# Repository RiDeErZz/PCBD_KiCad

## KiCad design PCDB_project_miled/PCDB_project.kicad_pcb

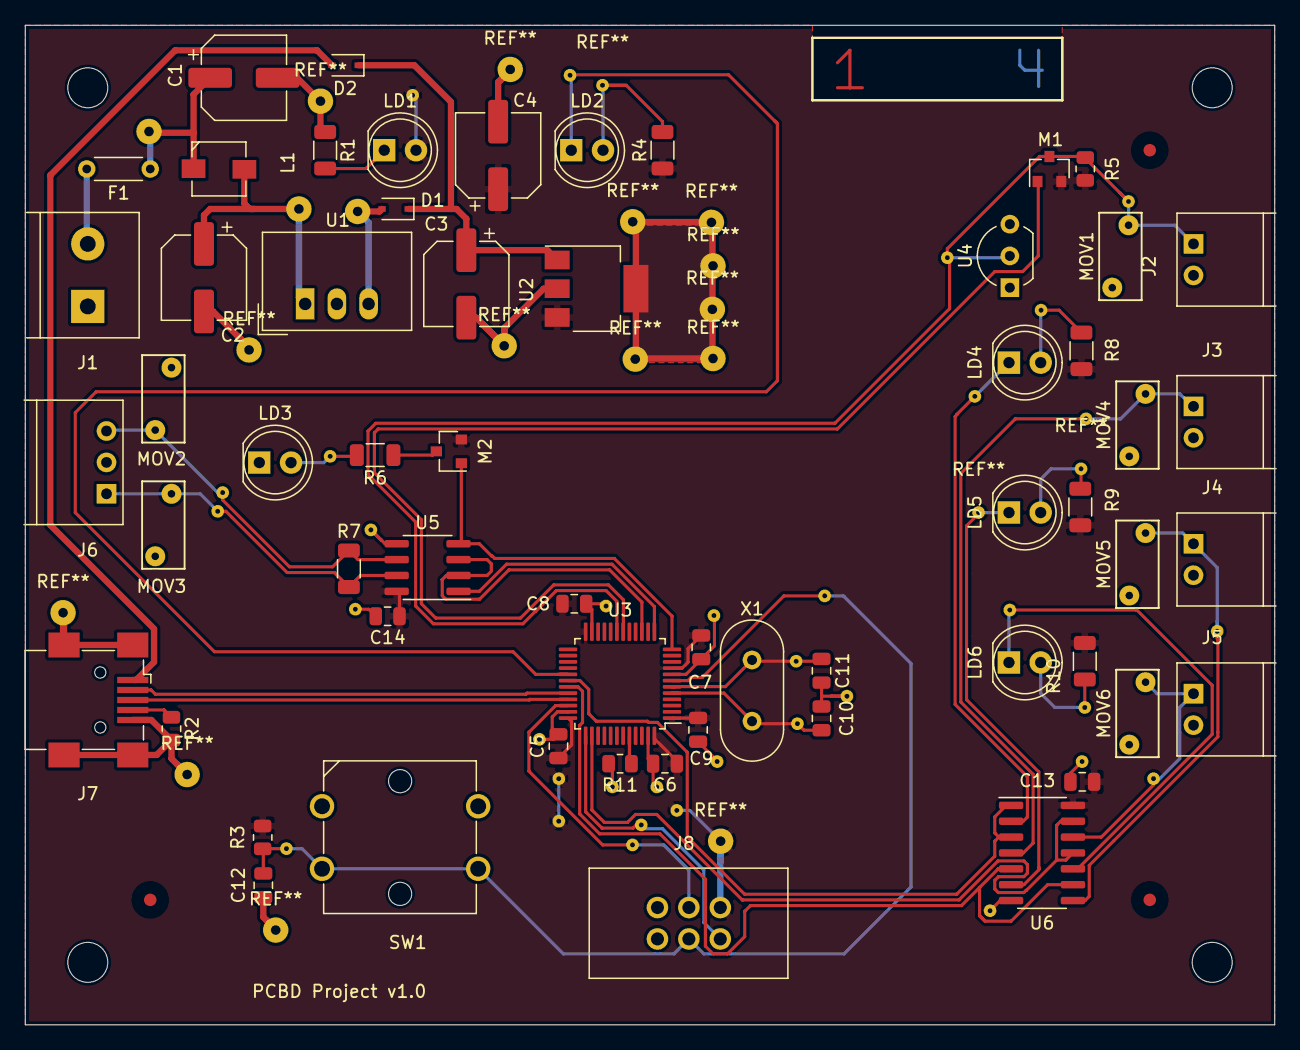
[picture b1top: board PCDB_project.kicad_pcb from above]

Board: 2 copper layers, 100.0 x 80.0 mm, 66 parts (0 on the bottom side), 41 nets.

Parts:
C1, C2, C3, C4: 10uF; CP_Elec_6.3x5.8
C5, C6, C7, C8, C9, C12, C13, C14: 100nF; C_0805_2012Metric
C10, C11: 20pF; C_0805_2012Metric
D1, D2: BAT60J; D_SOD-323
F1: 250mA; R_Axial_DIN0204_L3.6mm_D1.6mm_P5.08mm_Horizontal
FD1, FD2, FD3: Fiducial_1mm_Mask3mm
H1, H2, H3, H4: MountingHole_3.2mm_M3
J1: Power
J2, J3, J4, J5: 22-05-7025; IO2
J6: Comm; IO3
J7: USB_B_Mini; USB_Mini-B_Wuerth_65100516121_Horizontal
J8: Debug
L1: 5.6uH; tck141
LD1, LD6: Red; LED_D5.0mm
LD2: YELLOW; LED_D5.0mm
LD3: Green; LED_D5.0mm
LD4, LD5: Yellow; LED_D5.0mm
M1, M2: BSS84; SOT-23
MOV1, MOV2, MOV3, MOV4, MOV5, MOV6: MCFT000215; RV_Disc_D7mm_W3.4mm_P5mm
R1, R4, R6, R8, R9, R10: 330R; R_1206_3216Metric
R2, R11: 100k; R_0805_2012Metric
R3, R5: 4k7; R_0805_2012Metric
R7: 120R; R_1206_3216Metric
SW1: Reset; B3F-4000
U1: TSR_1-2450; Converter_DCDC_TRACO_TSR-1_THT
U2: UA78M33; SOT-223-3_TabPin2
U3: STM32F103CBT6; LQFP-48_7x7mm_P0.5mm
U4: DS1822-PAR; TO-92_Inline_Wide
U5: MAX3486; SOIC-8_3.9x4.9mm_P1.27mm
U6: MC74LCX07; SOIC-14_3.9x8.7mm_P1.27mm
X1: 8MHz; Crystal_HC18-U_Vertical

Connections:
+3V3: C4.1, C5.1, C6.1, C7.1, C8.1, C9.1, C13.1, C14.1, J8.1, LD1.2, M1.2, M2.2, R3.1, R4.1, R5.2, R8.1, R9.1, R10.1, U2.3, U3.1, U3.9, U3.24, U3.36, U3.48, U5.8, U6.14
/Supply/pwr1: F1.2, J1.2
/Supply/pwr2: C1.1, F1.1, L1.1
/Supply/pwr3: C2.1, L1.2, U1.1
/Supply/pwr4: D1.2, U1.3
/Supply/pwr5: C3.1, D1.1, D2.1, U2.1
ALARM_C: U3.38, U6.11, U6.13
DIR: U3.15, U5.2, U5.3
DQ: J2.1, M1.3, MOV1.1, R5.1, U3.19, U4.2
FAN1_C: U3.30, U6.1, U6.3
FAN2_C: U3.31, U6.5, U6.9
GATE: M1.1, U3.18
GND: C1.2, C2.2, C3.2, C4.2, C5.2, C6.2, C7.2, C8.2, C9.2, C10.2, C11.2, C12.2, C13.2, C14.2, J1.1, J2.2, J3.2, J4.2, J5.2, J6.2, J7.5, J7.6, J8.6, LD3.1, MOV1.2, MOV2.2, MOV3.2, MOV4.2, MOV5.2, MOV6.2, R1.1, R2.2, R11.2, SW1.1, U1.2, U2.2, U3.8, U3.23, U3.35, U3.47, U4.1, U5.5, U6.7
NRST: C12.1, J8.4, R3.2, SW1.2, U3.7
unnamed: C10.1, U3.5, X1.1
unnamed: C11.1, U3.6, X1.2
unnamed: J3.1, MOV4.1, U6.4
unnamed: J4.1, MOV5.1, U6.8
unnamed: J5.1, MOV6.1, U6.12
unnamed: J6.1, MOV3.1, R7.1, U5.7
unnamed: J6.3, MOV2.1, R7.2, U5.6
unnamed: J7.4, R2.1
unnamed: LD1.1, R1.2
unnamed: LD2.1, U3.29
unnamed: LD2.2, R4.2
unnamed: LD3.2, R6.2
unnamed: LD4.1, U6.2
unnamed: LD4.2, R8.2
unnamed: LD5.1, U6.6
unnamed: LD5.2, R9.2
unnamed: LD6.1, U6.10
unnamed: LD6.2, R10.2
unnamed: M2.3, R6.1
unnamed: R11.1, U3.44
RX: U3.13, U5.1
SWCLK: J8.2, U3.37
SWDIO: J8.3, U3.34
TX: M2.1, U3.12, U5.4
USB_DM: J7.2, U3.32
USB_DP: J7.3, U3.33
V_USB: D2.2, J7.1

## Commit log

2022-10-04 test
2022-10-04 restorationkicad
2022-10-18 Added footprint io2 and power
2022-10-18 Added IO3
2022-10-22 Footprint Añadidas pero no estoyseguro de que esén bien, falta update de esquemáticos y hacer BOM
2022-11-07 BOM añadido y comprobado las footprints, en principio estan bien. falta ocnfirmar con el profesor y medir el boton que parece que no estoy seguro si están bien hechos los pines
2022-11-08 Primera version de placement, bom coregido y footprints corregidas y verificadas
2022-11-08 Fixed components añadidos con buenas precision
2022-11-12 Placement acabado pero hay algunas dudas que resolver con el profe
2022-11-15 Correciones profe
2022-11-22 Enrutado conseguido pero hay alguna cosa que no me acab de gustar, nrst y chip de puertas logicas
2022-11-23 Proyecto basico acabado, hay que preguntar al profe un par de cosas mas del proyecto baisco para cerrarlo definitivamente
2022-11-26 Los dos opcionales hechos, falta responder dudas del profe y corregir fallos
2022-12-03 Version final PCDB
